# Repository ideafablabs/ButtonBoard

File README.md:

# 🔴 USB HID Button Board
breakout board for the Raspberry Pi Pico that allows connecting arcade buttons and outputing as a USB HID keyboard device. The firmware is built using Earle F. Philhower, III's Raspberry Pi Pico Arduino core and the standard Arduino IDE environment.

## ToDo:
* add mouse jiggler support
* add "macro" support
* add "custom key mappings" without re-flashing firmware
* add debounce support

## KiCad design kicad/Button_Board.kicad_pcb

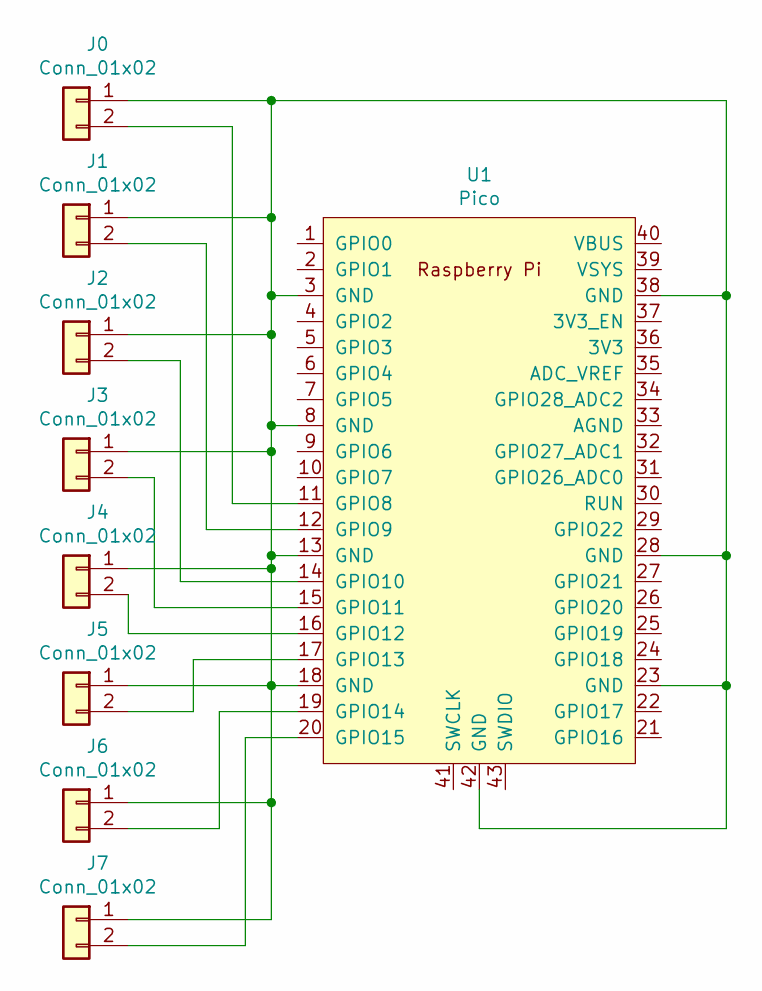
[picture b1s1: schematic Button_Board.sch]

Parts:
J0, J1, J2, J3, J4, J5, J6, J7: Conn_01x02; JST_XH_B2B-XH-A_1x02_P2.50mm_Vertical
U1: Pico; RPi_Pico_SMD_TH

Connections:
unnamed: J0.1, J1.1, J2.1, J3.1, J4.1, J5.1, J6.1, J7.1, U1.3 (GND), U1.8 (GND), U1.13 (GND), U1.18 (GND), U1.23 (GND), U1.28 (GND), U1.38 (GND), U1.42 (GND)
unnamed: J0.2, U1.11 (GPIO8)
unnamed: J1.2, U1.12 (GPIO9)
unnamed: J2.2, U1.14 (GPIO10)
unnamed: J3.2, U1.15 (GPIO11)
unnamed: J4.2, U1.16 (GPIO12)
unnamed: J5.2, U1.17 (GPIO13)
unnamed: J6.2, U1.19 (GPIO14)
unnamed: J7.2, U1.20 (GPIO15)

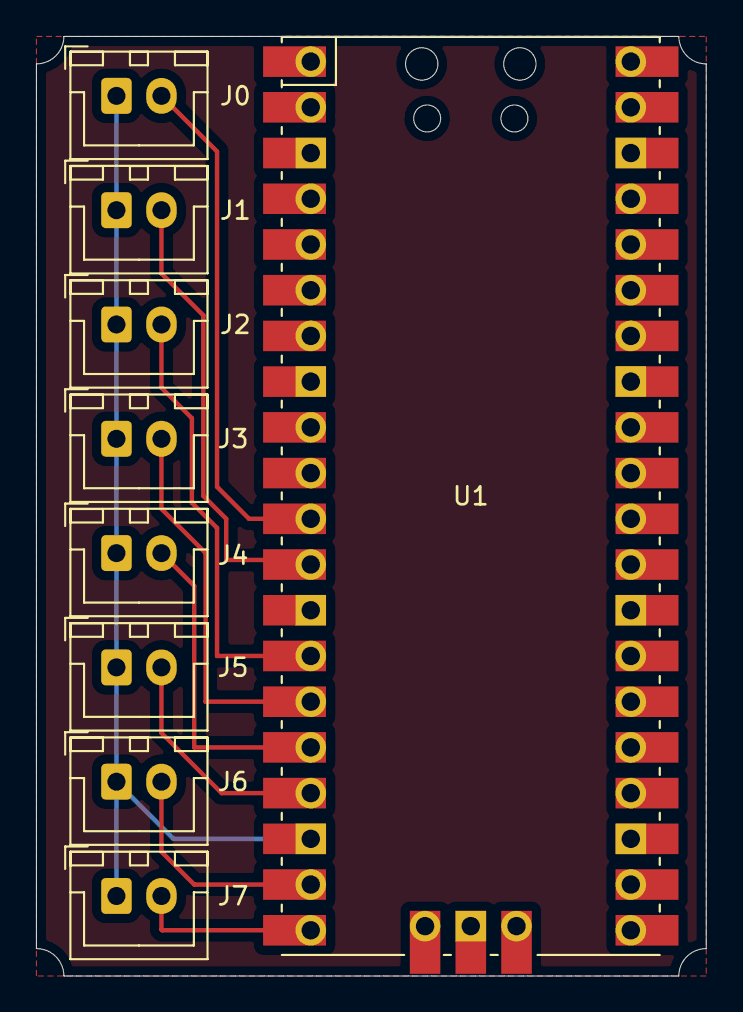
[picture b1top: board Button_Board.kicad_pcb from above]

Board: 2 copper layers, 37.2 x 52.2 mm, 9 parts (0 on the bottom side), 9 nets.

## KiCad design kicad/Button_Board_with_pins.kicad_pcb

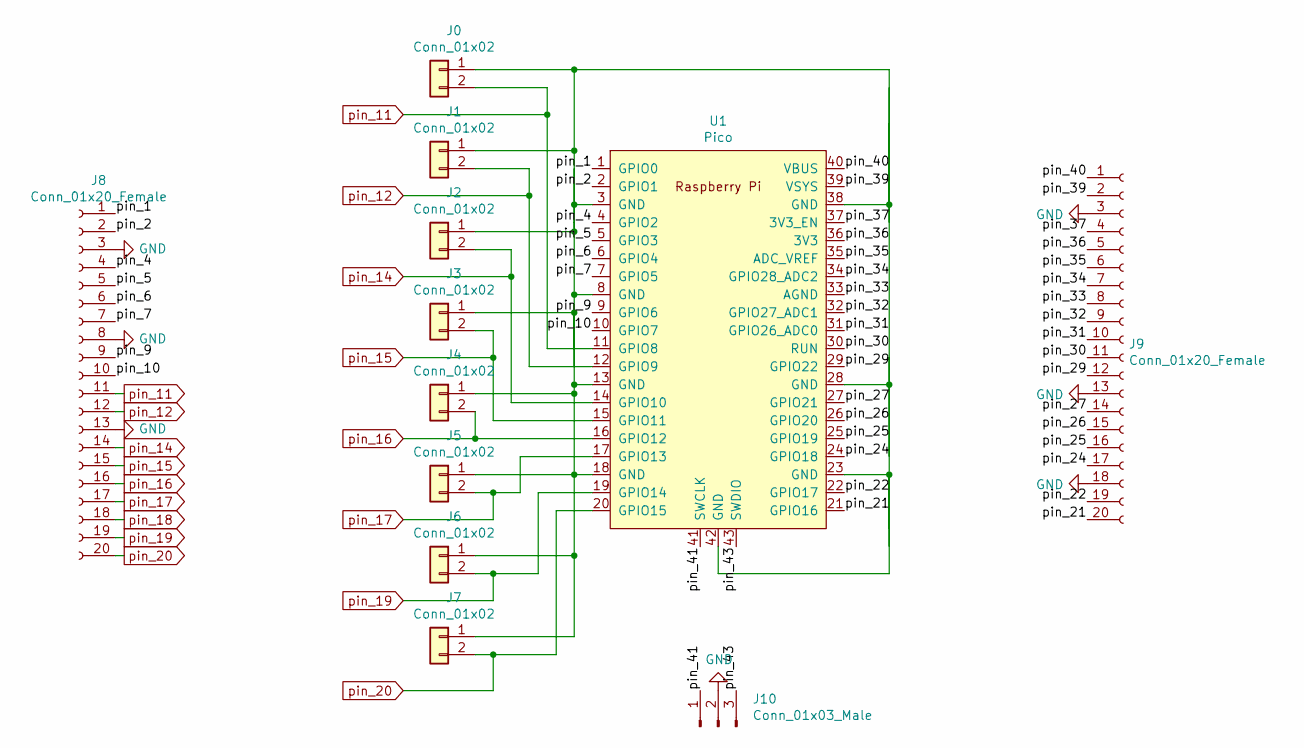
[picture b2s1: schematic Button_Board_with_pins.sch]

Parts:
J0, J1, J2, J3, J4, J5, J6, J7: Conn_01x02; JST_XH_B2B-XH-A_1x02_P2.50mm_Vertical
J8, J9: Conn_01x20_Female; PinSocket_1x20_P2.54mm_Vertical
J10: Conn_01x03_Male; PinHeader_1x03_P2.54mm_Vertical
U1: Pico; RPi_Pico_SMD_TH

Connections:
/pin_1: J8.1, U1.1 (GPIO0)
/pin_2: J8.2, U1.2 (GPIO1)
/pin_4: J8.4, U1.4 (GPIO2)
/pin_5: J8.5, U1.5 (GPIO3)
/pin_6: J8.6, U1.6 (GPIO4)
/pin_7: J8.7, U1.7 (GPIO5)
/pin_9: J8.9, U1.9 (GPIO6)
/pin_10: J8.10, U1.10 (GPIO7)
/pin_21: J9.20, U1.21 (GPIO16)
/pin_22: J9.19, U1.22 (GPIO17)
/pin_24: J9.17, U1.24 (GPIO18)
/pin_25: J9.16, U1.25 (GPIO19)
/pin_26: J9.15, U1.26 (GPIO20)
/pin_27: J9.14, U1.27 (GPIO21)
/pin_29: J9.12, U1.29 (GPIO22)
/pin_30: J9.11, U1.30 (RUN)
/pin_31: J9.10, U1.31 (GPIO26_ADC0)
/pin_32: J9.9, U1.32 (GPIO27_ADC1)
/pin_33: J9.8, U1.33 (AGND)
/pin_34: J9.7, U1.34 (GPIO28_ADC2)
/pin_35: J9.6, U1.35 (ADC_VREF)
/pin_36: J9.5, U1.36 (3V3)
/pin_37: J9.4, U1.37 (3V3_EN)
/pin_39: J9.2, U1.39 (VSYS)
/pin_40: J9.1, U1.40 (VBUS)
/pin_41: J10.1, U1.41 (SWCLK)
/pin_43: J10.3, U1.43 (SWDIO)
GND: J8.3, J8.8, J8.13, J9.3, J9.13, J9.18, J10.2
unnamed: J0.1, J1.1, J2.1, J3.1, J4.1, J5.1, J6.1, J7.1, U1.3 (GND), U1.8 (GND), U1.13 (GND), U1.18 (GND), U1.23 (GND), U1.28 (GND), U1.38 (GND), U1.42 (GND)
pin_11: J0.2, J8.11, U1.11 (GPIO8)
pin_12: J1.2, J8.12, U1.12 (GPIO9)
pin_14: J2.2, J8.14, U1.14 (GPIO10)
pin_15: J3.2, J8.15, U1.15 (GPIO11)
pin_16: J4.2, J8.16, U1.16 (GPIO12)
pin_17: J5.2, J8.17, U1.17 (GPIO13)
pin_18: J8.18
pin_19: J6.2, J8.19, U1.19 (GPIO14)
pin_20: J7.2, J8.20, U1.20 (GPIO15)

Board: 2 copper layers, 12 parts (0 on the bottom side), 37 nets, no tracks yet.

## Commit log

2022-02-16 Add Files
    Add Files
2022-02-18 case2
2022-04-07 Add files via upload
    ver-4
2022-04-07 Add files via upload
    gcode
2022-05-23 Add files via upload
    added UF2 file for easy install
2025-03-26 Vibe Coded debounce and shortpress
    // Buttons 1 and 2 support long press (persistent key)
    // Buttons 3-8 send only one keystroke per press event.
    // Debounce delay set to 50 milliseconds
